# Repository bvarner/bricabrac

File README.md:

# bicabrac
Oddities and Objects I design

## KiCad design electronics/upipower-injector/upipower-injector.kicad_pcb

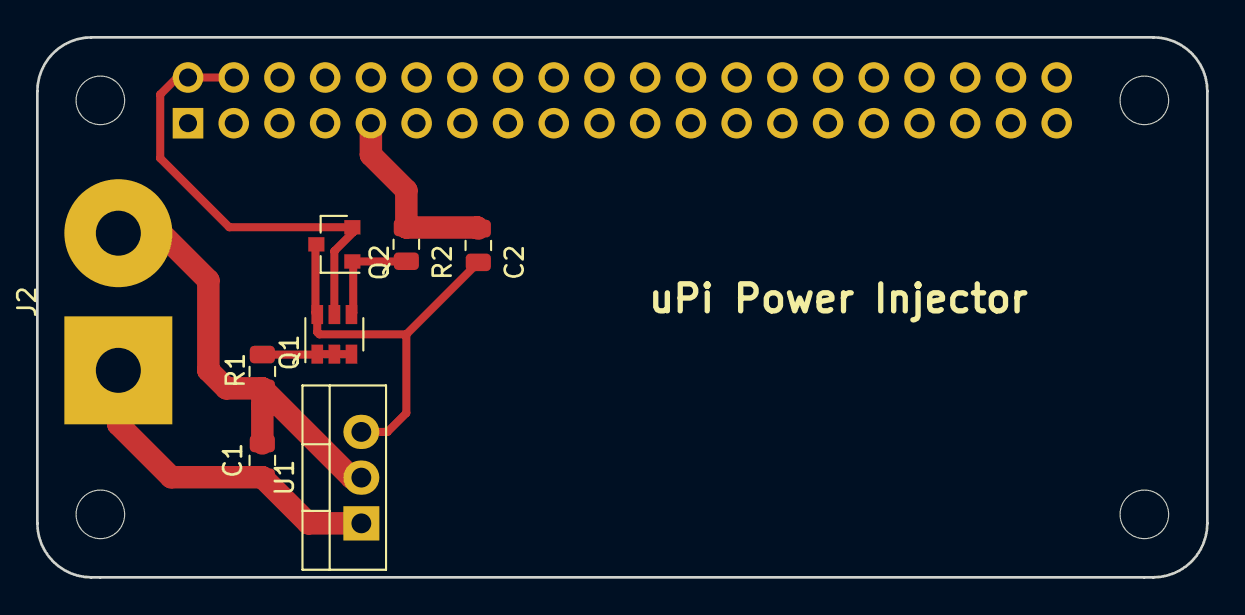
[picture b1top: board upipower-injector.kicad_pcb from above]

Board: 2 copper layers, 65.0 x 30.0 mm, 13 parts (1 on the bottom side), 7 nets.

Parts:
C1, C2: 10uf; C_0805_2012Metric
H1, H2, H3, H4: MountingHole; MountingHole_2.7mm_M2.5_uHAT_RPi
J1: GPIO_CONNECTOR; PinSocket_2x20_P2.54mm_Vertical_Centered_Anchor
J2: Conn_01x02_Female; SolderWirePad_1x02_P7.62mm_Drill2.5mm
Q1: DMMT5401; SOT-23-6
Q2: DMG2305UX-13; SOT-23
R1: 10K; R_0805_2012Metric
R2: 47K; R_0805_2012Metric
U1: LM7805_TO220; TO-220-3_Vertical

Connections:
+3V3: J1.1, J1.17
+5V: J1.2, J1.4, Q1.5, Q2.2
+12V: C1.1, J2.1, U1.1
GND: C1.2, C2.2, J1.6, J1.9, J1.14, J1.20, J1.25, J1.30, J1.34, J1.39, J2.2, R1.2, R2.2, U1.2
unnamed: C2.1, Q1.6, Q2.3, U1.3
unnamed: Q1.1, Q1.2, Q1.3, R1.1
unnamed: Q1.4, Q2.1, R2.1

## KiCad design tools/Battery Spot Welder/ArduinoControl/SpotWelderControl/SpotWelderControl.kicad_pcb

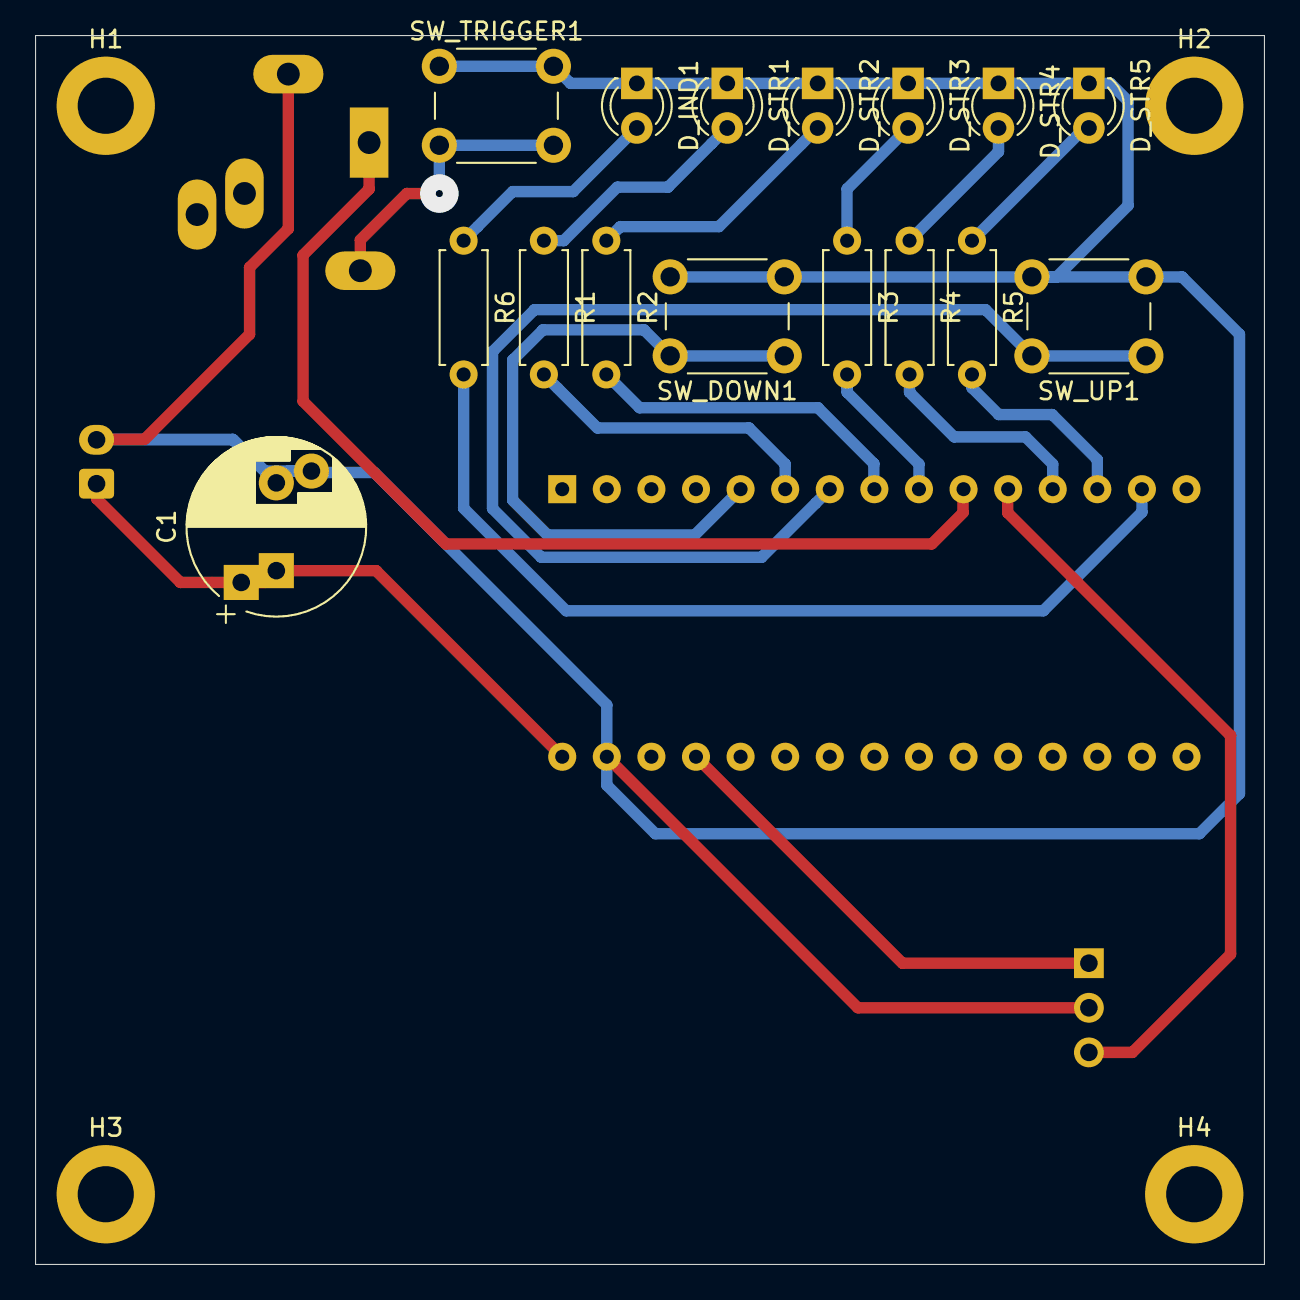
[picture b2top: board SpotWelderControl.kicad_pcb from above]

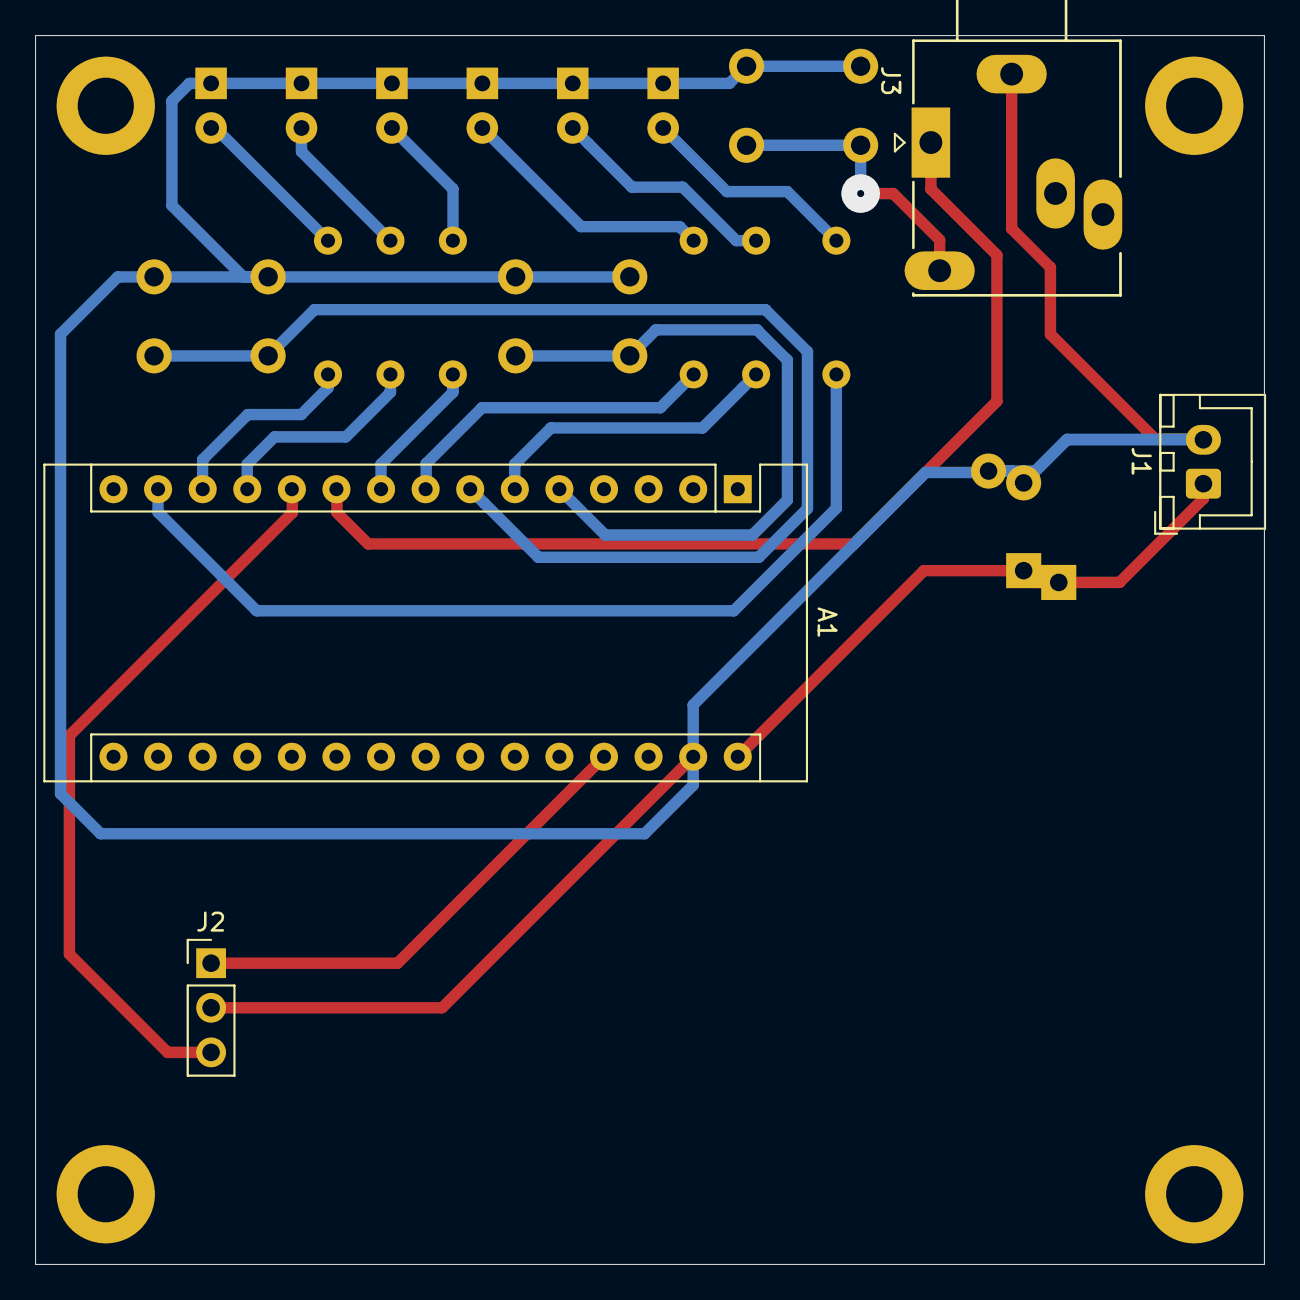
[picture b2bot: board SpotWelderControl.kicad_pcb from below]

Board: 2 copper layers, 70.0 x 70.0 mm, 24 parts (4 on the bottom side), 20 nets.

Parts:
A1: Arduino_Nano_v3.x; Arduino_Nano
C1: 1000uF 25VDC; CP_Radial_D10.0mm_P5.00mm_P7.50mm
D_IND1: LED; LED_D3.0mm
D_STR1, D_STR2, D_STR3, D_STR4, D_STR5: LED; LED_D3.0mm
H1, H2, H3, H4: MountingHole; MountingHole_3.2mm_M3_DIN965_Pad
J1: 12v Power; JST_XH_B2B-XH-A_1x02_P2.50mm_Vertical
J2: RELAY; PinHeader_1x03_P2.54mm_Vertical
J3: AudioJack2_Switch; Jack_3.5mm_Ledino_KB3SPRS_Horizontal
R1, R2, R3, R4, R5, R6: 1k; R_Axial_DIN0207_L6.3mm_D2.5mm_P7.62mm_Horizontal
SW_DOWN1: SW_SPST; SW_PUSH_6mm
SW_TRIGGER1: SW_SPST; SW_PUSH_6mm
SW_UP1: SW_SPST; SW_PUSH_6mm

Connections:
+12V: A1.30, C1.1, J1.1
GND: A1.29, C1.2, D_IND1.1, D_STR1.1, D_STR2.1, D_STR3.1, D_STR4.1, D_STR5.1, J1.2, J2.2, J3.S, SW_DOWN1.2, SW_TRIGGER1.1, SW_UP1.2
unnamed: A1.5, SW_DOWN1.1
unnamed: A1.6, R1.2
unnamed: A1.7, SW_UP1.1
unnamed: A1.8, R2.2
unnamed: A1.9, R3.2
unnamed: A1.10, J3.T
unnamed: A1.11, J2.3
unnamed: A1.12, R4.2
unnamed: A1.13, R5.2
unnamed: A1.14, R6.2
unnamed: A1.27, J2.1
unnamed: D_IND1.2, R6.1
unnamed: D_STR1.2, R1.1
unnamed: D_STR2.2, R2.1
unnamed: D_STR3.2, R3.1
unnamed: D_STR4.2, R4.1
unnamed: D_STR5.2, R5.1
unnamed: J3.TN, SW_TRIGGER1.2

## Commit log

2019-02-06 Adding the pi_camera_v1_gopro_m12 case.
2019-02-06 Pushing the American Flyer stuff I made over the holidays
2019-02-06 Adding a bunch of things I've done over the last year.
2019-02-07 Updated to actually fit a gopro mount better.
2019-02-07 Forgot to add these last night, updates to the size of the project case, tweak for camera ribbon cable location.
2019-02-08 Added a wall anchor for my boys target, and updated the rocketstand case.
2019-02-12 Updates to the inner form support. Improves airflow, dosen't obstruct vent holes, uses far less filament.
2019-02-18 Major updates to the ramming bits. I've been able to properly form hydraulic cement nozzles, and it looks _nice_.
2019-02-26 Updates to the forms. Many, Updates.
2019-07-31 I've created a printable replacement chassis for ARES Recon (HD) FPV Drones.
    My kid picked one up for a steal, and broke it within hours.
    For ~13 grams of PETG, I can print as many replacements as he needs.
2019-07-31 * Updates to the drone nacell friction tight sizing. * Made the wire guides more robust, added secondardy guides. * Reinforced the FPV antenna mount. * Resized the LED hole to be a bit tighter.
2019-08-01 Updated the drone frame. First printed version!
2019-08-01 * Nacelle Placement now correct. * Moved battery box screws to the top. No longer need to flip things to print. * Tweaks to the motor fitment of the nacelle bottoms. * Other small fixes I do not reme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
2019-08-02 * Better cutout support (to reduce weight) for the larger battery size.
2019-08-02 * Adjusted the SD card cut.
2019-08-02 * Updated the renderings.
2019-08-02 * Thinned the battery bottom to reduce weight. Probably should have left this at 4 layers. * Added a 'hook' to the battery rubber-band locks.
2019-08-22 * Updates ot he FPV first iteration frame * cog (center of gravity) remix... * Moves the battery lower, protects it better. * Puts the video board further away from the main controller, which seemed 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
2019-08-31 * Added a mold for hot-glue injection moulding of rubber landing bumpers. * Center-Of-Gravity rework for 802540 batteries is freaking awesome. * Battery compartment for 802540's giving more options f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
2019-10-08 Adding drone progress.
2019-10-08 Some initial work on reverse engineering things.
2019-10-08 Updating to run openscad on the cli...
2019-10-09 Updates with better traced paths.
2019-10-09 Rendered. The SCAD to STL.
2019-10-09 Fixed up the latch tolerances.
2019-10-14 Added the spot welding parts.:
2019-10-15 Added the battery spot welder pen. It could use a few tweaks, but this works well.
2019-10-16 * Updated the upper-half of the LiIon pack. The top was tapering in a very wonky manner. * Welding pen. For when you're making your own spot welder. :-D * ArduinoControl for the spot welder. I used a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
2019-10-17 KiCad project carrier board for arduino nano and single-channel relay.
2019-10-21 Added a large capacitor to the arduino controller. Should keep voltage drop during the pulse to a minimum, and allow the controller to keep running. Added the panel buttons and relay standoff support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
2019-10-29 Tweaks due to printing and fitment issues.
2019-12-08 Some ancilliary updates.
2019-12-08 Added 0.25mm nozzle optimized STLs for the top and the charge / non-charge indicator bottoms.
2019-12-11 Current Iteration.
2019-12-12 Include an indent into the bottom, so that we can add a label and hopefully reduce bottom warp.
2019-12-12 Modifications for making permutations, because. Niiiice.
2019-12-12 Because it's nice to have CPU to do my normal things while this is running....
2019-12-12 minor fix
2019-12-13 Many little updates.
2019-12-13 Not sure how, but deleted an option.
2019-12-13 Updated Renders
2019-12-21 For some reason the screw holes didn't render in several places. Yikes.
2019-12-22 * Pretty Print the inside of the tower with a graduated change to the final shape.
2020-02-11 Updated for the newer style latch spring.
2020-02-11 Updated to include the wider spring base option.
2020-02-12 Updating the render script and scad.
2020-02-12 Updates with wide spring support.
2020-02-13 Update to the bottom wide spring retainer.
2020-02-25 Adding my s-x-12 psu cover remix. Yuck this hack.
2020-04-06 Added the Whirlpool filter dummy.
2020-04-06 Made it longer. Because... it was missing the support in the fridge.
2020-04-08 A rather large commit / push. I got lazy about adding things.
2020-04-13 Quite happy with this setup for the 4" PVC Inlet / Outlet drain.
2020-04-13 Updated readme.
2020-05-02 Updates. Yo.
2020-05-02 Remove the air vent. We really don't need this.
2020-05-02 Some things I made for the hydroponic rig based on 4 inch PVC
2020-07-09 I've been busy...
2020-08-19 Added a bolt knob and the HVLP filter first draft.
2020-08-20 Updated the HVLP
2020-08-25 Added the router-bit-storage solution.
    Print the inserts with TPU, and the base in your favorite heat-tolerant filament.
2021-03-19 Major Epic Push.
2021-03-19 * Overhangless printing! * Upper lip now smoothly transitions to eliminate overhang. * Feet glue-in works perfectly. * Lower boxes in a stack formation without divisions get indents to hold / stop th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
2021-06-23 Some HF bins and my desk lamp remix.
2021-06-29 1/2 BSP thread hose connector. bilge hose o-rings for a Bestway above ground pool. Hayward maxflo pool pump o-ring Pool bubbler (Aerator) from a Dyson DC25 vacuum motor. bestway pool cup holders. Con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
2021-06-30 Mechanical retention of the electrical connector built into the top cap.
2021-08-27 Minor update to the laptop stand to make it larger and have a better center of gravity under a laptop. Adjustments to the storage bin -- better geometry and loads of tiny improvements.
2021-09-16 Added some more stuff.
2021-10-26 Added a makerbeam compatible Tee-Nut. This can save you a bunch o' money if you're using makerbeam...
    Pool hose to PVC adapter - inside diameter of PVC version. This will be helpful for the 'bubbler' but also for winterization.
2022-01-22 Added a tool to hold things for installing cabinet crown trim.
2022-05-12 Adding these...
2022-05-27 Added Optimus Prime Hip
2022-06-06 Updates.
2022-06-08 Designed a dust shroud for ye ole' delta planer. 3 parts. Printable. In Fusion360... Will export project files later.
2022-06-09 fix: Adjusted hole locations. fix: Updated sizes for zip ties. fix: Outer frame thickness properly specified.
2022-06-09 Tweaked zip tie sizing and location.
2022-06-09 Zip Tie Location Update
2022-06-14 Updates...
2022-06-26 Final export
2022-07-30 The Varnerized Stencil Machine.
2023-03-21 feat: Added a new clip for hanging a whiteboard.
2025-07-09 feat: A few odds and ends.

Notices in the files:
electronics/upipower-injector/upipower-injector.kicad_pcb:
This PCB design is licensed under MIT Open Source License.
